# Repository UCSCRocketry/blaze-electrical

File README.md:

# blaze electrical
UC Santa Cruz Rocket Team's unified high power rocketry avionics project, electrical repository

[Notion Project Managment (Private)](https://ucscrocketry.notion.site/)

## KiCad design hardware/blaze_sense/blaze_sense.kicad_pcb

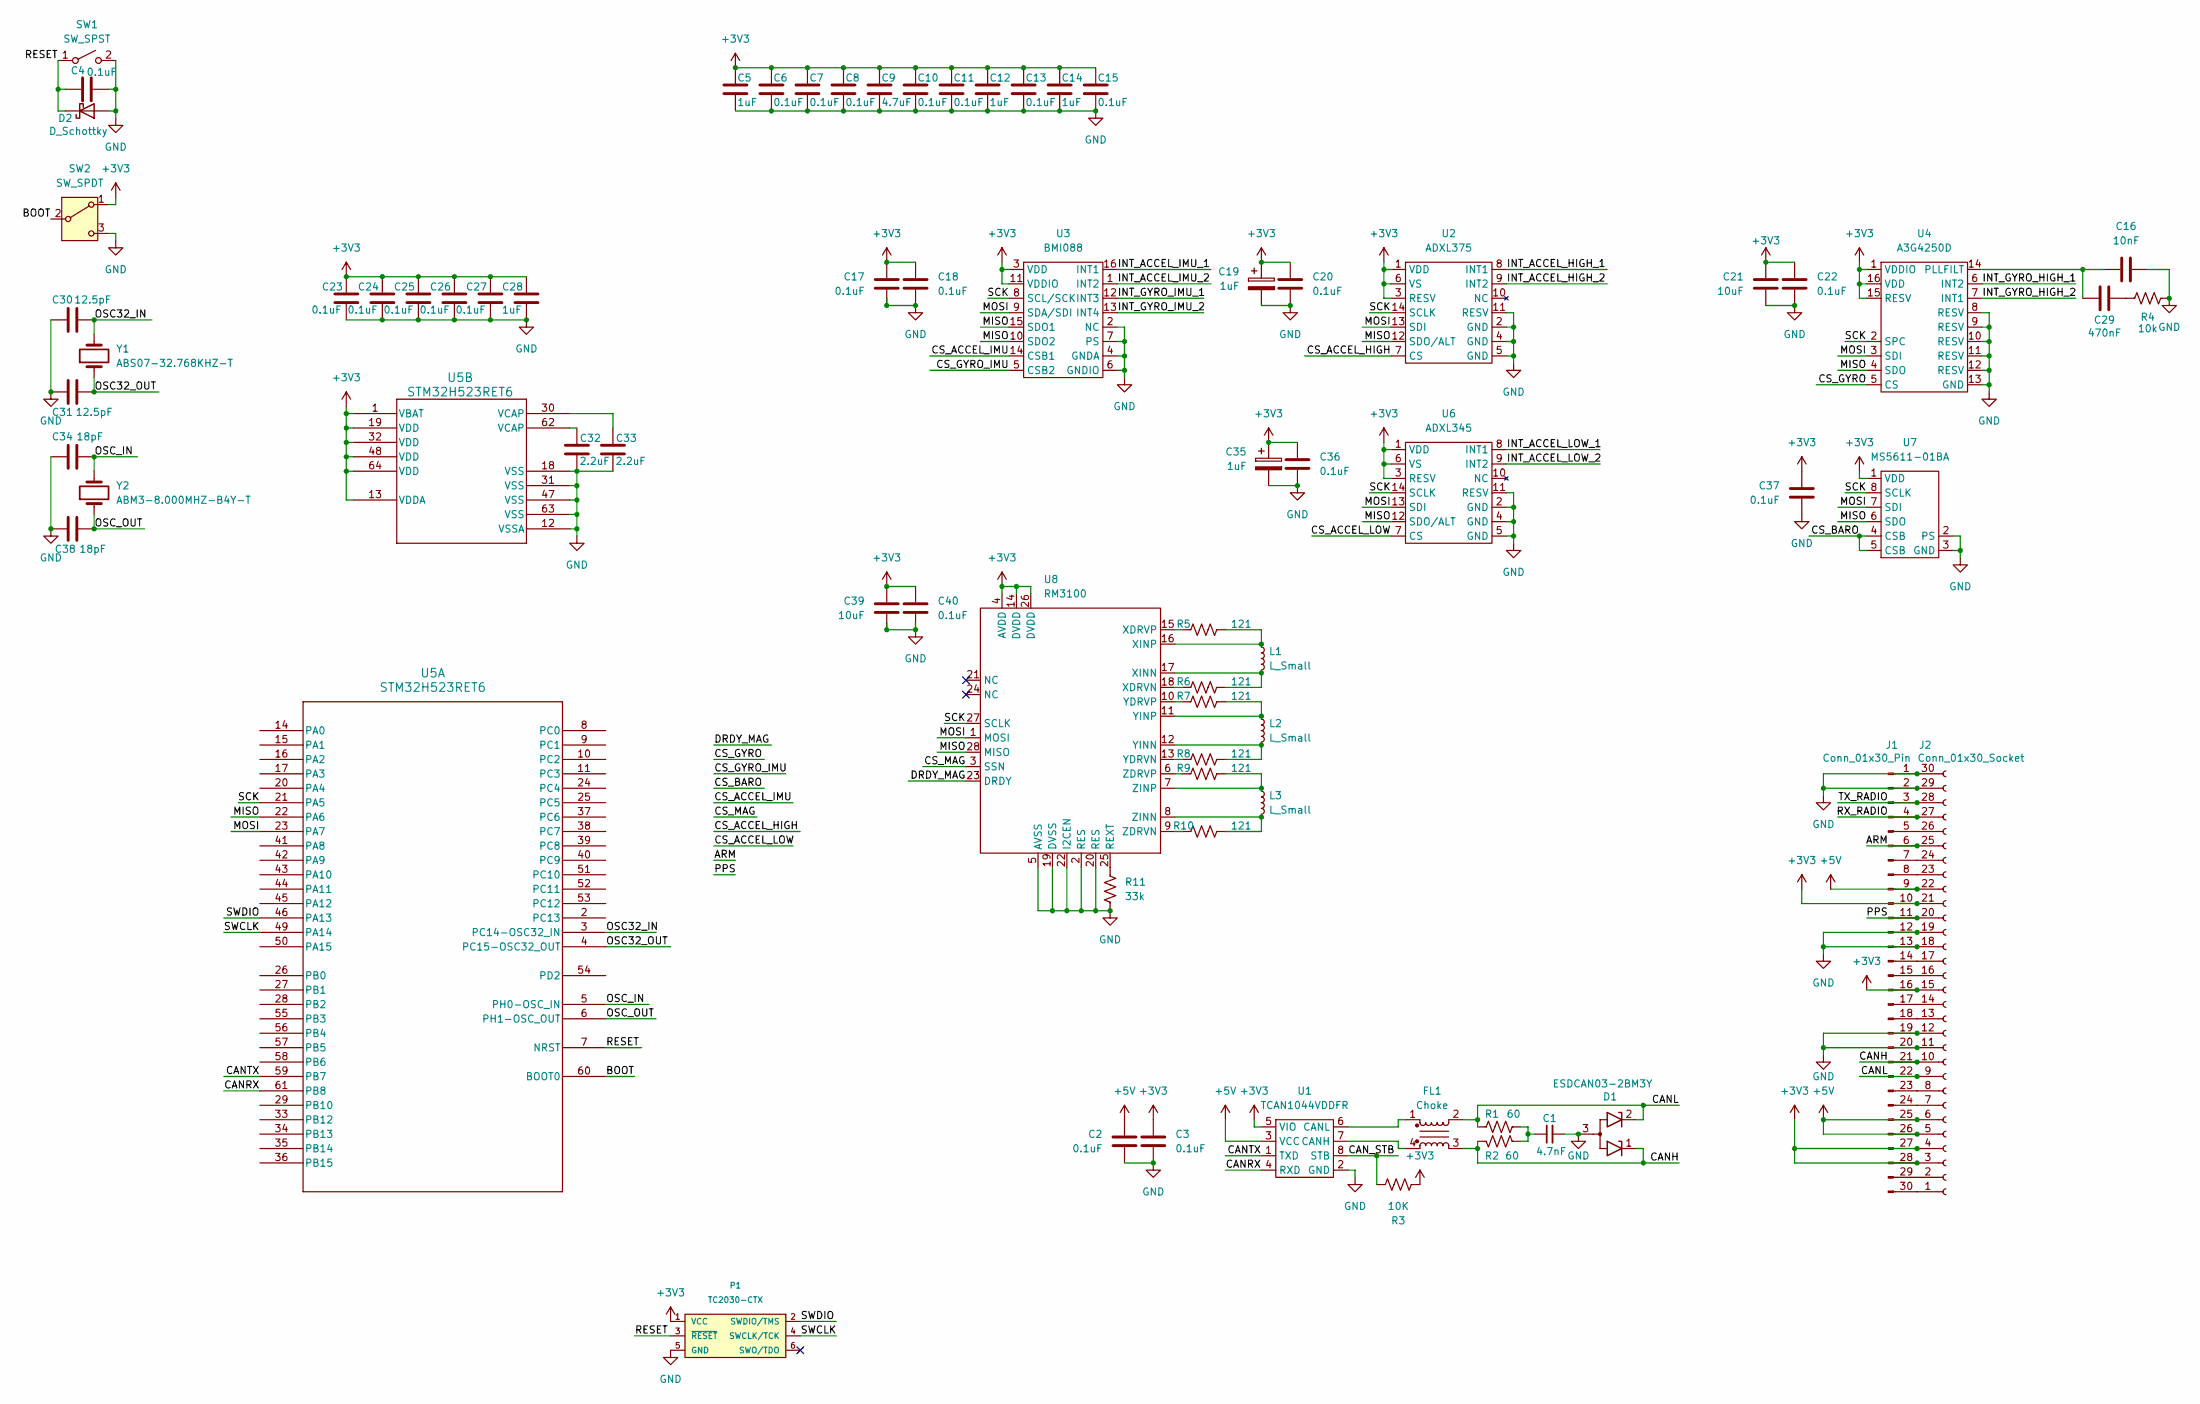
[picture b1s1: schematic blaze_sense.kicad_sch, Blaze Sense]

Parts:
C1: 4.7nF; C_0603_1608Metric
C2, C3, C4, C6, C7, C8, C10, C11, C13, C15, C17, C18, C20, C22, C23, C24, C25, C26, C27, C36, C37, C40: 0.1uF; C_0603_1608Metric
C5, C12, C14, C19, C28, C35: 1uF; C_0603_1608Metric
C9: 4.7uF; C_0603_1608Metric
C16: 10nF; C_0603_1608Metric
C21, C39: 10uF; C_0603_1608Metric
C29: 470nF; C_0603_1608Metric
C30, C31: 12.5pF; C_0603_1608Metric
C32, C33: 2.2uF; C_0603_1608Metric
C34, C38: 18pF; C_0603_1608Metric
D1: ESDCAN03-2BM3Y; SOT-416
D2: D_Schottky; D_0603_1608Metric
FL1: Choke; L_CommonModeChoke_Coilcraft_0603USB
J1: Conn_01x30_Pin; HRS_DF17_1.0H_-30DP-0.5V_57_
J2: Conn_01x30_Socket; HRS_DF17_1.0H_-30DP-0.5V_57_
L1, L2: L_Small; SENSOR-XY-F-RM3100
L3: L_Small; SENSOR-Z-F-RM3100
P1: TC2030-CTX; TC2030-IDC-FP
R1, R2: 60; R_0603_1608Metric
R3: 10K; R_0603_1608Metric
R4: 10k; R_0603_1608Metric
R5, R6, R7, R8, R9, R10: 121; R_0603_1608Metric
R11: 33k; R_0603_1608Metric
SW1: SW_SPST; SW_SPST_B3U-1000P
SW2: SW_SPDT; Nidec_Copal_CAS-120A
U1: TCAN1044VDDFR; Texas_VSON-HR-8_1.5x2mm_P0.5mm
U2: ADXL375; ADXL375BCCZ-RL
U3: BMI088
U4: A3G4250D
U5: STM32H523RET6; LQFP64_STM
U6: ADXL345
U7: MS5611-01BA; LGA-8_3x5mm_P1.25mm
U8: RM3100; RM3100-13156
Y1: ABS07-32.768KHZ-T; Crystal_SMD_3215-2Pin_3.2x1.5mm
Y2: ABM3-8.000MHZ-B4Y-T; Crystal_SMD_3215-2Pin_3.2x1.5mm

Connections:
+3V3: C3.1, C5.1, C6.1, C7.1, C8.1, C9.1, C10.1, C11.1, C12.1, C13.1, C14.1, C15.1, C17.1, C18.1, C19.1, C20.1, C21.1, C22.1, C23.1, C24.1, C25.1, C26.1, C27.1, C28.1, C35.1, C36.1, C37.1, C39.1, C40.1, J1.10, J1.16, J1.27, J1.28, J2.3, J2.4, J2.15, J2.21, P1.1 (VCC), R3.2, SW2.1 (A), U1.5 (VIO), U2.1 (VDD), U2.3 (RESV), U2.6 (VS), U3.3 (VDD), U3.11 (VDDIO), U4.1 (VDDIO), U4.15 (RESV), U4.16 (VDD), U5.1 (VBAT), U5.13 (VDDA), U5.19 (VDD), U5.32 (VDD), U5.48 (VDD), U5.64 (VDD), U6.1 (VDD), U6.3 (RESV), U6.6 (VS), U7.1 (VDD), U8.4 (AVDD), U8.14 (DVDD), U8.26 (DVDD)
+5V: C2.1, J1.9, J1.25, J1.26, J2.5, J2.6, J2.22, U1.3 (VCC)
/ARM: J1.6, J2.25
/BOOT: SW2.2 (B), U5.60 (BOOT0)
/CANH: D1.1 (K1), FL1.3, J1.21, J2.10, R2.1
/CANL: D1.2 (K2), FL1.2, J1.22, J2.9, R1.1
/CANRX: U1.4 (RXD), U5.61 (PB8)
/CANTX: U1.1 (TXD), U5.59 (PB7)
/CAN_STB: R3.1, U1.8 (STB)
/CS_ACCEL_HIGH: U2.7 (CS)
/CS_ACCEL_IMU: U3.14 (CSB1)
/CS_ACCEL_LOW: U6.7 (CS)
/CS_BARO: U7.4 (CSB), U7.5 (CSB)
/CS_GYRO: U4.5 (CS)
/CS_GYRO_IMU: U3.5 (CSB2)
/CS_MAG: U8.3 (SSN)
/DRDY_MAG: U8.23 (DRDY)
/INT_ACCEL_HIGH_1: U2.8 (INT1)
/INT_ACCEL_HIGH_2: U2.9 (INT2)
/INT_ACCEL_IMU_1: U3.16 (INT1)
/INT_ACCEL_IMU_2: U3.1 (INT2)
/INT_ACCEL_LOW_1: U6.8 (INT1)
/INT_ACCEL_LOW_2: U6.9 (INT2)
/INT_GYRO_HIGH_1: U4.6 (INT2)
/INT_GYRO_HIGH_2: U4.7 (INT1)
/INT_GYRO_IMU_1: U3.12 (INT3)
/INT_GYRO_IMU_2: U3.13 (INT4)
/MISO: U2.12 (SDO/ALT), U3.10 (SDO2), U3.15 (SDO1), U4.4 (SDO), U5.22 (PA6), U6.12 (SDO/ALT), U7.6 (SDO), U8.28 (MISO)
/MOSI: U2.13 (SDI), U3.9 (SDA/SDI), U4.3 (SDI), U5.23 (PA7), U6.13 (SDI), U7.7 (SDI), U8.1 (MOSI)
/OSC32_IN: C30.2, U5.3 (PC14-OSC32_IN), Y1.2
/OSC32_OUT: C31.2, U5.4 (PC15-OSC32_OUT), Y1.1
/OSC_IN: C34.2, U5.5 (PH0-OSC_IN), Y2.2
/OSC_OUT: C38.2, U5.6 (PH1-OSC_OUT), Y2.1
/PPS: J1.11, J2.20
/RESET: C4.1, D2.1 (K), P1.3 (~RESET), SW1.1 (A), U5.7 (NRST)
/RX_RADIO: J1.4, J2.27
/SCK: U2.14 (SCLK), U3.8 (SCL/SCK), U4.2 (SPC), U5.21 (PA5), U6.14 (SCLK), U7.8 (SCLK), U8.27 (SCLK)
/SWCLK: P1.4 (SWCLK/TCK), U5.49 (PA14)
/SWDIO: P1.2 (SWDIO/TMS), U5.46 (PA13)
/TX_RADIO: J1.3, J2.28
GND: C1.2, C2.2, C3.2, C4.2, C5.2, C6.2, C7.2, C8.2, C9.2, C10.2, C11.2, C12.2, C13.2, C14.2, C15.2, C16.2, C17.2, C18.2, C19.2, C20.2, C21.2, C22.2, C23.2, C24.2, C25.2, C26.2, C27.2, C28.2, C30.1, C31.1, C32.2, C33.2, C34.1, C35.2, C36.2, C37.2, C38.1, C39.2, C40.2, D1.3 (A), D2.2 (A), J1.1, J1.2, J1.12, J1.13, J1.19, J1.20, J2.11, J2.12, J2.18, J2.19, J2.29, J2.30, P1.5 (GND), R4.2, R11.2, SW1.2 (B), SW2.3 (C), U1.2 (GND), U2.2 (GND), U2.4 (GND), U2.5 (GND), U2.11 (RESV), U3.2 (NC), U3.4 (GNDA), U3.6 (GNDIO), U3.7 (PS), U4.8 (RESV), U4.9 (RESV), U4.10 (RESV), U4.11 (RESV), U4.12 (RESV), U4.13 (GND), U5.12 (VSSA), U5.18 (VSS), U5.31 (VSS), U5.47 (VSS), U5.63 (VSS), U6.2 (GND), U6.4 (GND), U6.5 (GND), U6.11 (RESV), U7.2 (PS), U7.3 (GND), U8.2 (RES), U8.5 (AVSS), U8.19 (DVSS), U8.20 (RES), U8.22 (I2CEN)
unnamed: C1.1, R1.2, R2.2
unnamed: C29.2, R4.1
unnamed: C32.1, U5.62 (VCAP)
unnamed: C33.1, U5.30 (VCAP)
unnamed: J1.5, J2.26
unnamed: J1.7, J2.24
unnamed: J1.8, J2.23
unnamed: J1.14, J2.17
unnamed: J1.15, J2.16
unnamed: J1.17, J2.14
unnamed: J1.18, J2.13
unnamed: J1.23, J2.8
unnamed: J1.24, J2.7
unnamed: J1.29, J2.2
unnamed: J1.30, J2.1
unnamed: FL1.4, U1.7 (CANH)
unnamed: FL1.1, U1.6 (CANL)
unnamed: C16.1, C29.1, U4.14 (PLLFILT)
unnamed: R11.1, U8.25 (REXT)
unnamed: R6.1, U8.18 (XDRVN)
unnamed: R5.1, U8.15 (XDRVP)
unnamed: L1.2, R6.2, U8.17 (XINN)
unnamed: L1.1, R5.2, U8.16 (XINP)
unnamed: R8.1, U8.13 (YDRVN)
unnamed: R7.1, U8.10 (YDRVP)
unnamed: L2.2, R8.2, U8.12 (YINN)
unnamed: L2.1, R7.2, U8.11 (YINP)
unnamed: R10.1, U8.9 (ZDRVN)
unnamed: R9.1, U8.6 (ZDRVP)
unnamed: L3.2, R10.2, U8.8 (ZINN)
unnamed: L3.1, R9.2, U8.7 (ZINP)

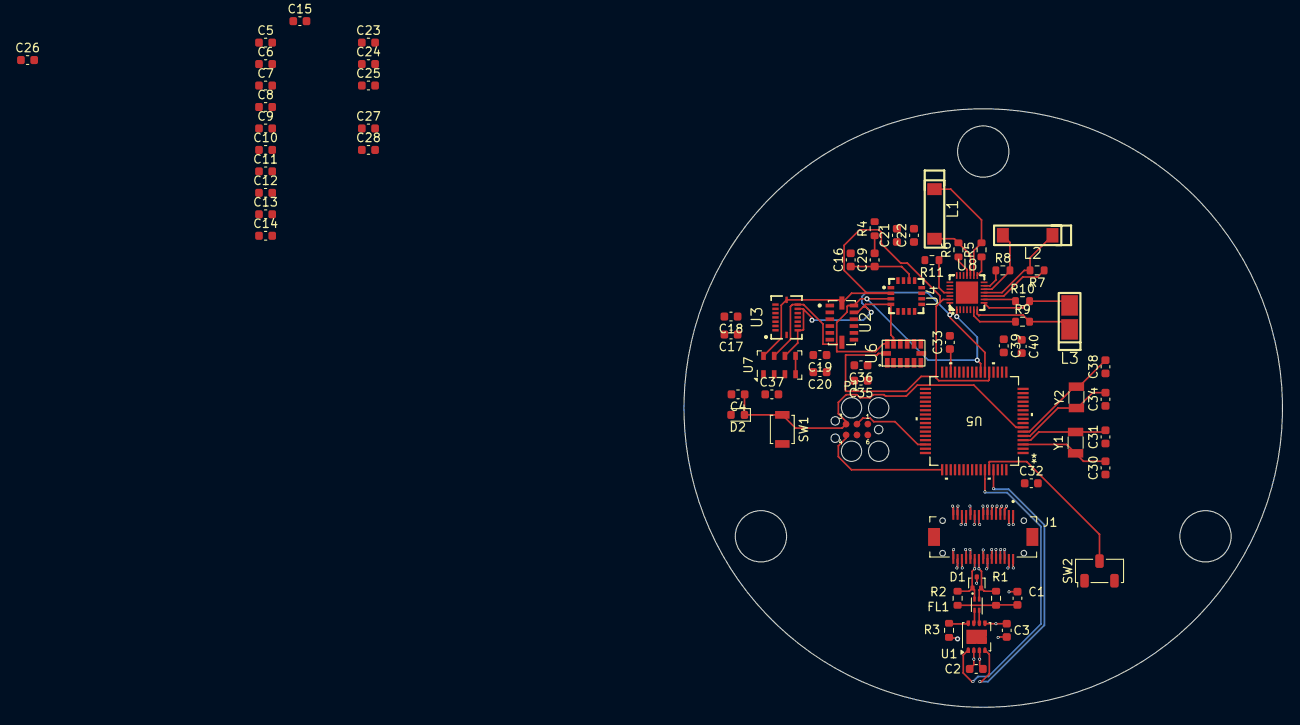
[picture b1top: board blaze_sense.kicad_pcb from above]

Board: 4 copper layers, 70.0 x 70.0 mm, 72 parts (1 on the bottom side), 55 nets.

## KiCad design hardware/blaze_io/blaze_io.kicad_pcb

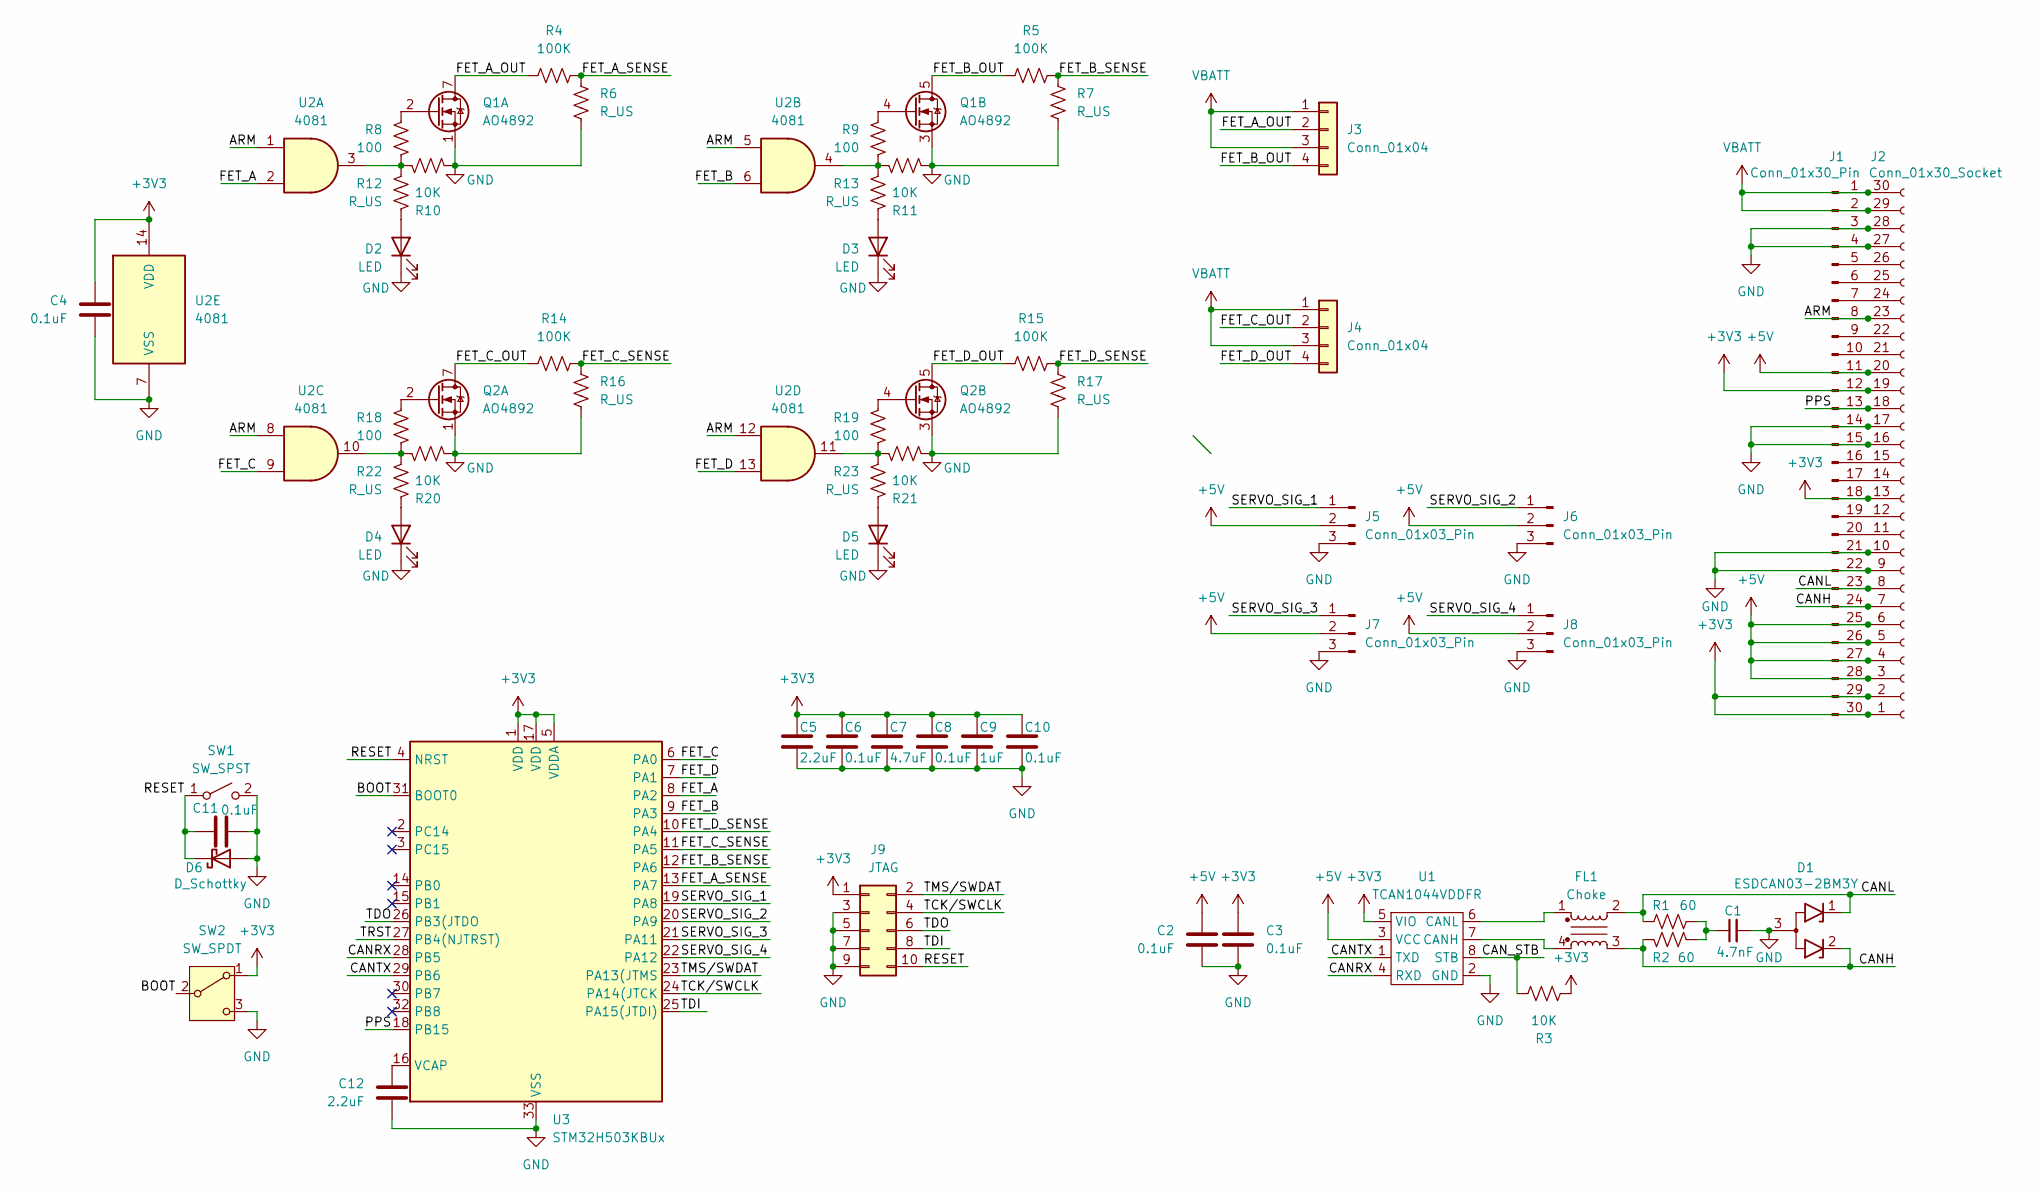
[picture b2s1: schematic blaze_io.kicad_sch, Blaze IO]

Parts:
C1: 4.7nF; C_0603_1608Metric
C2, C3, C4, C6, C8, C10, C11: 0.1uF; C_0603_1608Metric
C5, C12: 2.2uF; C_0603_1608Metric
C7: 4.7uF; C_0603_1608Metric
C9: 1uF; C_0603_1608Metric
D1: ESDCAN03-2BM3Y; SOT-416
D2, D3, D4, D5: LED; LED_0603_1608Metric
D6: D_Schottky; D_0603_1608Metric
FL1: Choke; L_CommonModeChoke_Coilcraft_0603USB
J1: Conn_01x30_Pin; HRS_DF17_1.0H_-30DP-0.5V_57_
J2: Conn_01x30_Socket; HRS_DF17_1.0H_-30DP-0.5V_57_
J3, J4: Conn_01x04; TerminalBlock_TE_282834-4_1x04_P2.54mm_Horizontal
J5, J6, J7, J8: Conn_01x03_Pin; PinHeader_1x03_P2.54mm_Vertical
J9: JTAG; PinHeader_2x05_P2.54mm_Vertical
Q1, Q2: AO4892; SOIC-8_3.9x4.9mm_P1.27mm
R1, R2: 60; R_0603_1608Metric
R3, R10, R11, R20, R21: 10K; R_0603_1608Metric
R4, R5, R14, R15: 100K; R_0603_1608Metric
R6, R7, R12, R13, R16, R17, R22, R23: R_US; R_0603_1608Metric
R8, R9, R18, R19: 100; R_0603_1608Metric
SW1: SW_SPST; SW_SPST_B3U-1000P
SW2: SW_SPDT; Nidec_Copal_CAS-120A
U1: TCAN1044VDDFR; Texas_VSON-HR-8_1.5x2mm_P0.5mm
U2: 4081; SOIC-14_3.9x8.7mm_P1.27mm
U3: STM32H503KBUx; QFN-32-1EP_5x5mm_P0.5mm_EP3.45x3.45mm

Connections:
+3V3: C3.1, C4.1, C5.1, C6.1, C7.1, C8.1, C9.1, C10.1, J1.12, J1.18, J1.29, J1.30, J2.1, J2.2, J2.13, J2.19, J9.1, R3.2, SW2.1 (A), U1.5 (VIO), U2.14 (VDD), U3.1 (VDD), U3.5 (VDDA), U3.17 (VDD)
+5V: C2.1, J1.11, J1.25, J1.26, J1.27, J1.28, J2.3, J2.4, J2.5, J2.6, J2.20, J5.2, J6.2, J7.2, J8.2, U1.3 (VCC)
/ARM: J1.8, J2.23, U2.1, U2.5, U2.8, U2.12
/BOOT: SW2.2 (B), U3.31 (BOOT0)
/CANH: D1.2 (K2), FL1.3, J1.24, J2.7, R2.1
/CANL: D1.1 (K1), FL1.2, J1.23, J2.8, R1.1
/CANRX: U1.4 (RXD), U3.28 (PB5)
/CANTX: U1.1 (TXD), U3.29 (PB6)
/CAN_STB: R3.1, U1.8 (STB)
/FET_A: U2.2, U3.8 (PA2)
/FET_A_OUT: J3.2, Q1.7 (D1), Q1.8 (D1), R4.1
/FET_A_SENSE: R4.2, R6.2, U3.13 (PA7)
/FET_B: U2.6, U3.9 (PA3)
/FET_B_OUT: J3.4, Q1.5 (D2), Q1.6 (D2), R5.1
/FET_B_SENSE: R5.2, R7.2, U3.12 (PA6)
/FET_C: U2.9, U3.6 (PA0)
/FET_C_OUT: J4.2, Q2.7 (D1), Q2.8 (D1), R14.1
/FET_C_SENSE: R14.2, R16.2, U3.11 (PA5)
/FET_D: U2.13, U3.7 (PA1)
/FET_D_OUT: J4.4, Q2.5 (D2), Q2.6 (D2), R15.1
/FET_D_SENSE: R15.2, R17.2, U3.10 (PA4)
/PPS: J1.13, J2.18, U3.18 (PB15)
/RESET: C11.1, D6.1 (K), J9.10, SW1.1 (A), U3.4 (NRST)
/SERVO_SIG_1: J5.1, U3.19 (PA8)
/SERVO_SIG_2: J6.1, U3.20 (PA9)
/SERVO_SIG_3: J7.1, U3.21 (PA11)
/SERVO_SIG_4: J8.1, U3.22 (PA12)
/TCK/SWCLK: J9.4, U3.24 (PA14(JTCK)
/TDI: J9.8, U3.25 (PA15(JTDI))
/TDO: J9.6, U3.26 (PB3(JTDO)
/TMS/SWDAT: J9.2, U3.23 (PA13(JTMS)
/TRST: U3.27 (PB4(NJTRST))
GND: C1.2, C2.2, C3.2, C4.2, C5.2, C6.2, C7.2, C8.2, C9.2, C10.2, C11.2, C12.2, D1.3 (A), D2.1 (K), D3.1 (K), D4.1 (K), D5.1 (K), D6.2 (A), J1.3, J1.4, J1.14, J1.15, J1.21, J1.22, J2.9, J2.10, J2.16, J2.17, J2.27, J2.28, J5.3, J6.3, J7.3, J8.3, J9.3, J9.5, J9.7, J9.9, Q1.1 (S1), Q1.3 (S2), Q2.1 (S1), Q2.3 (S2), R6.1, R7.1, R10.2, R11.2, R16.1, R17.1, R20.2, R21.2, SW1.2 (B), SW2.3 (C), U1.2 (GND), U2.7 (VSS), U3.33 (VSS)
unnamed: C1.1, R1.2, R2.2
unnamed: D2.2 (A), R12.2
unnamed: D3.2 (A), R13.2
unnamed: D4.2 (A), R22.2
unnamed: D5.2 (A), R23.2
unnamed: J1.5, J2.26
unnamed: J1.6, J2.25
unnamed: J1.7, J2.24
unnamed: J1.9, J2.22
unnamed: J1.10, J2.21
unnamed: J1.16, J2.15
unnamed: J1.17, J2.14
unnamed: J1.19, J2.12
unnamed: J1.20, J2.11
unnamed: Q1.2 (G1), R8.1
unnamed: Q1.4 (G2), R9.1
unnamed: Q2.2 (G1), R18.1
unnamed: Q2.4 (G2), R19.1
unnamed: R8.2, R10.1, R12.1, U2.3
unnamed: R9.2, R11.1, R13.1, U2.4
unnamed: R18.2, R20.1, R22.1, U2.10
unnamed: R19.2, R21.1, R23.1, U2.11
unnamed: FL1.4, U1.7 (CANH)
unnamed: FL1.1, U1.6 (CANL)
unnamed: C12.1, U3.16 (VCAP)
VBATT: J1.1, J1.2, J2.29, J2.30, J3.1, J3.3, J4.1, J4.3

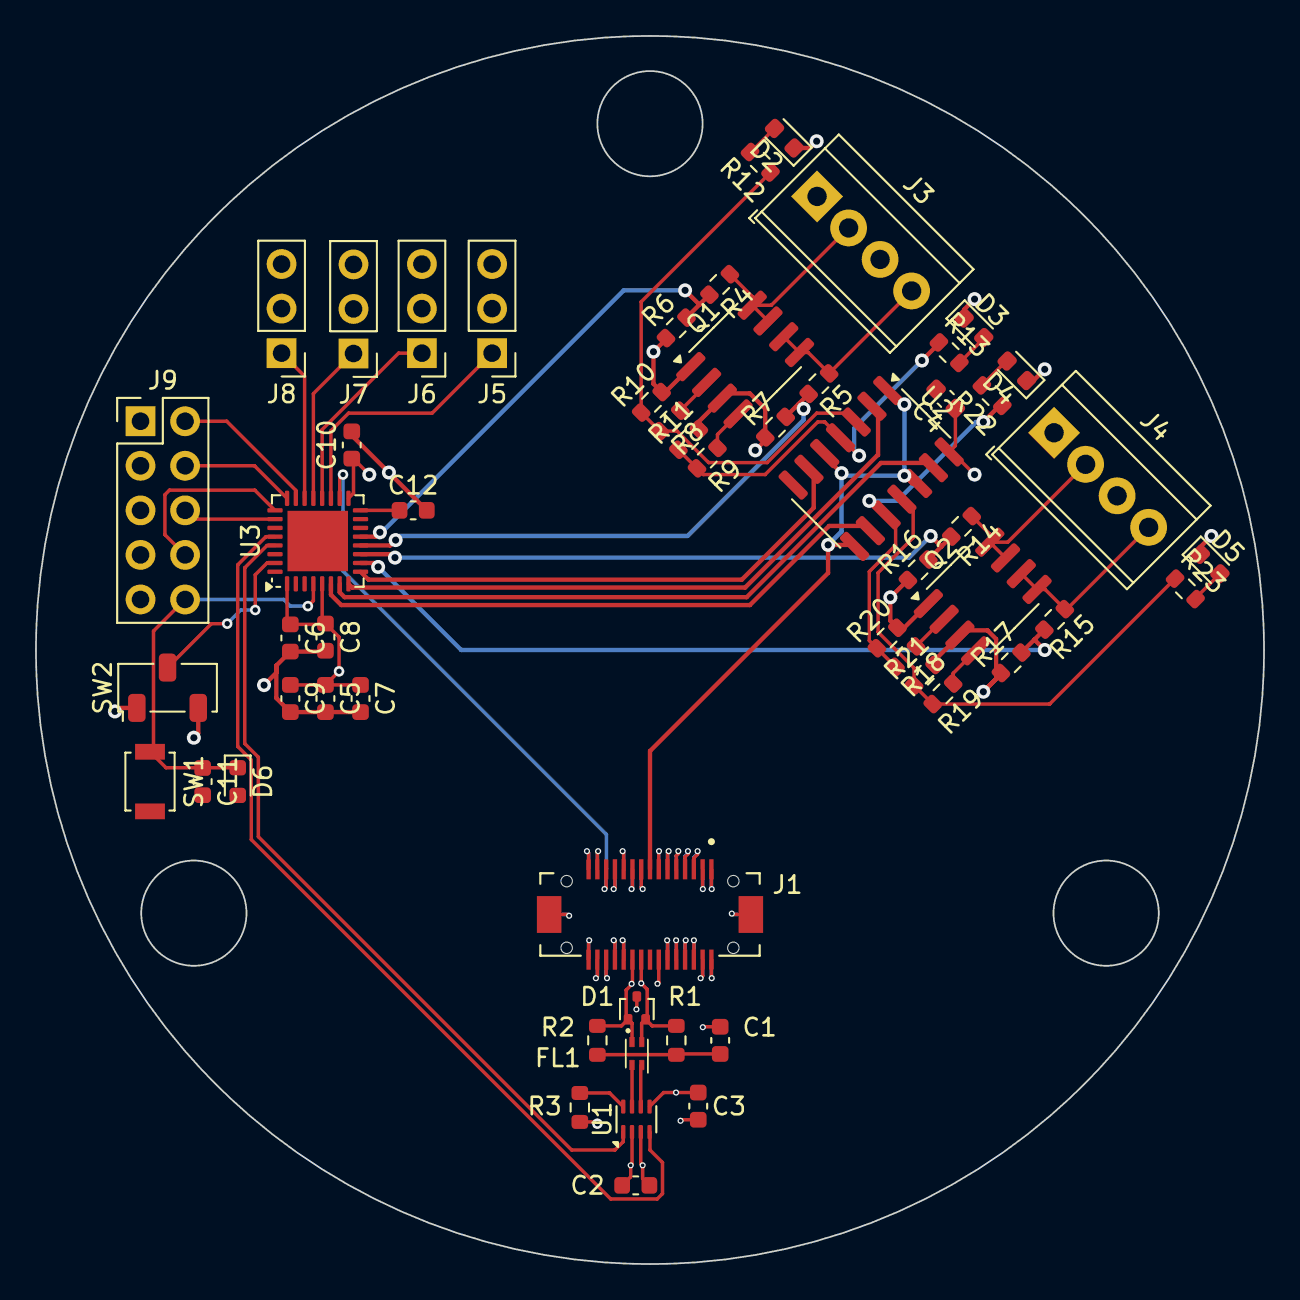
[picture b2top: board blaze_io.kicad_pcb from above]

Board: 4 copper layers, 70.0 x 70.0 mm, 58 parts (1 on the bottom side), 58 nets.

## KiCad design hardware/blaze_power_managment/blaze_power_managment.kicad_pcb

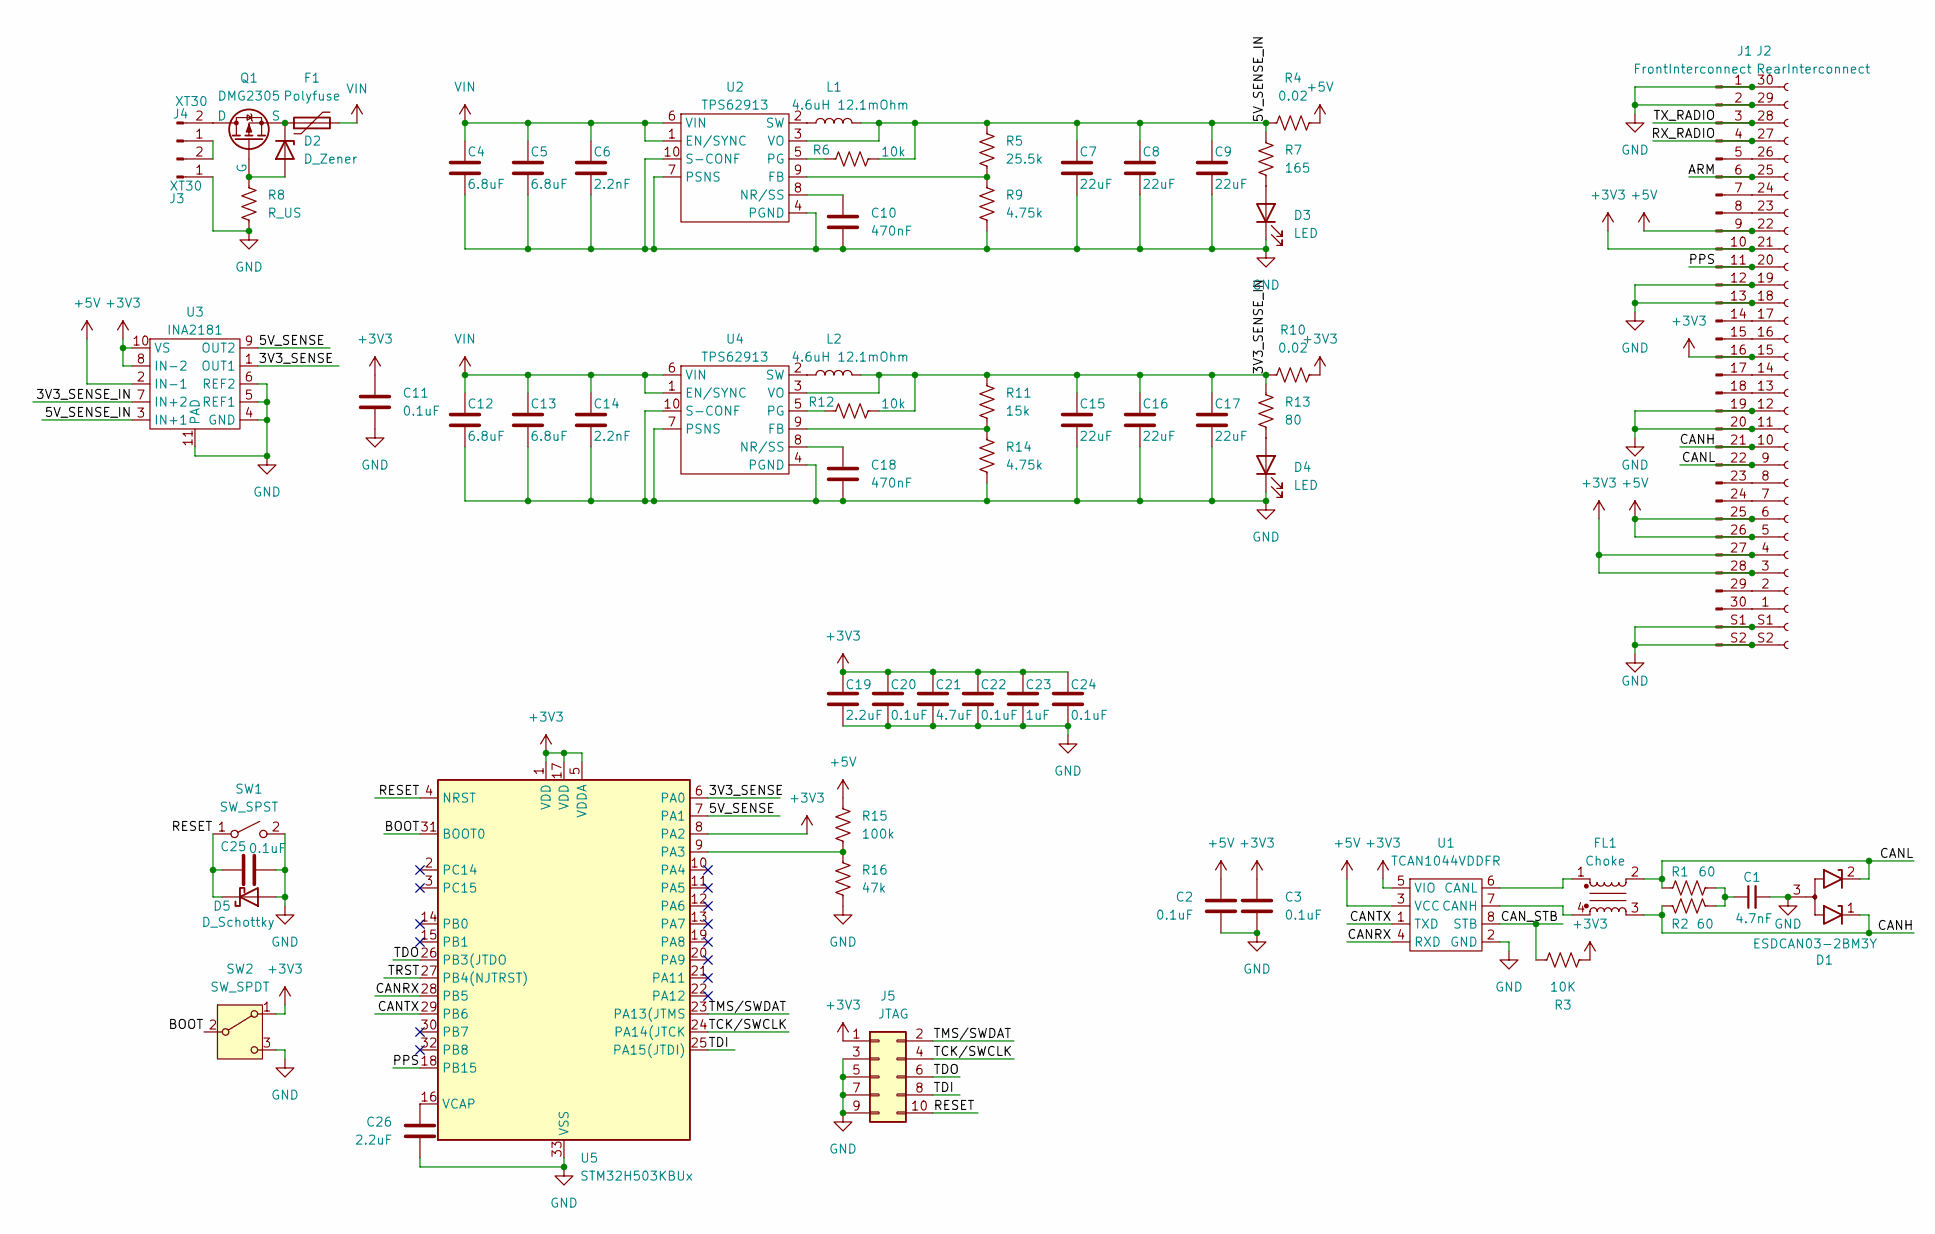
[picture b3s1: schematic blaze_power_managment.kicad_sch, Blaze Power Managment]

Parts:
C1: 4.7nF; C_0603_1608Metric
C2, C3, C11, C20, C22, C24, C25: 0.1uF; C_0603_1608Metric
C4, C5, C12, C13: 6.8uF; C_0603_1608Metric
C6, C14: 2.2nF; C_0603_1608Metric
C7, C8, C9, C15, C16, C17: 22uF; C_0603_1608Metric
C10, C18: 470nF; C_0603_1608Metric
C19, C26: 2.2uF; C_0603_1608Metric
C21: 4.7uF; C_0603_1608Metric
C23: 1uF; C_0603_1608Metric
D1: ESDCAN03-2BM3Y; SOT-416
D2: D_Zener; D_0603_1608Metric
D3, D4: LED; LED_0603_1608Metric
D5: D_Schottky; D_0603_1608Metric
F1: Polyfuse; Fuse_1206_3216Metric
FL1: Choke; L_CommonModeChoke_Coilcraft_0603USB
J1: FrontInterconnect; HRS_DF17_1.0H_-30DP-0.5V_57_
J2: RearInterconnect; HRS_DF17_1.0H_-30DP-0.5V_57_
J3, J4: XT30; AMASS_XT30PW-M_1x02_P2.50mm_Horizontal
J5: JTAG; PinHeader_2x05_P1.00mm_Vertical_SMD
L1, L2: 4.6uH 12.1mOhm; L_SXN_SMDRI124
Q1: DMG2305; SOT-23-3
R1, R2: 60; R_0603_1608Metric
R3: 10K; R_0603_1608Metric
R4, R10: 0.02; R_0603_1608Metric
R5: 25.5k; R_0603_1608Metric
R6, R12: 10k; R_0603_1608Metric
R7: 165; R_0603_1608Metric
R8: R_US; R_0603_1608Metric
R9, R14: 4.75k; R_0603_1608Metric
R11: 15k; R_0603_1608Metric
R13: 80; R_0603_1608Metric
R15: 100k; R_0603_1608Metric
R16: 47k; R_0603_1608Metric
SW1: SW_SPST; SW_SPST_B3U-1000P
SW2: SW_SPDT; Nidec_Copal_CAS-120A
U1: TCAN1044VDDFR; Texas_VSON-HR-8_1.5x2mm_P0.5mm
U2, U4: TPS62913; TPS62913R
U3: INA2181; WSON10-DSQ0010A_TEX
U5: STM32H503KBUx; QFN-32-1EP_5x5mm_P0.5mm_EP3.45x3.45mm

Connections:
+3V3: C3.1, C11.1, C19.1, C20.1, C21.1, C22.1, C23.1, C24.1, J1.10, J1.16, J1.27, J1.28, J2.3, J2.4, J2.15, J2.21, J5.1, R3.2, R10.2, SW2.1 (A), U1.5 (VIO), U3.8 (IN-2), U3.10 (VS), U5.1 (VDD), U5.5 (VDDA), U5.8 (PA2), U5.17 (VDD)
+5V: C2.1, J1.9, J1.25, J1.26, J2.5, J2.6, J2.22, R4.2, R15.1, U1.3 (VCC), U3.2 (IN-1)
/3V3_SENSE: U3.1 (OUT1), U5.6 (PA0)
/3V3_SENSE_IN: C15.1, C16.1, C17.1, L2.2, R10.1, R11.1, R12.2, R13.1, U3.7 (IN+2), U4.3 (VO)
/5V_SENSE: U3.9 (OUT2), U5.7 (PA1)
/5V_SENSE_IN: C7.1, C8.1, C9.1, L1.2, R4.1, R5.1, R6.2, R7.1, U2.3 (VO), U3.3 (IN+1)
/ARM: J1.6, J2.25
/BOOT: SW2.2 (B), U5.31 (BOOT0)
/CANH: D1.1 (K1), FL1.3, J1.21, J2.10, R2.1
/CANL: D1.2 (K2), FL1.2, J1.22, J2.9, R1.1
/CANRX: U1.4 (RXD), U5.28 (PB5)
/CANTX: U1.1 (TXD), U5.29 (PB6)
/CAN_STB: R3.1, U1.8 (STB)
/PPS: J1.11, J2.20, U5.18 (PB15)
/RESET: C25.1, D5.1 (K), J5.10, SW1.1 (A), U5.4 (NRST)
/RX_RADIO: J1.4, J2.27
/TCK/SWCLK: J5.4, U5.24 (PA14(JTCK)
/TDI: J5.8, U5.25 (PA15(JTDI))
/TDO: J5.6, U5.26 (PB3(JTDO)
/TMS/SWDAT: J5.2, U5.23 (PA13(JTMS)
/TRST: U5.27 (PB4(NJTRST))
/TX_RADIO: J1.3, J2.28
GND: C1.2, C2.2, C3.2, C4.2, C5.2, C6.2, C7.2, C8.2, C9.2, C10.2, C11.2, C12.2, C13.2, C14.2, C15.2, C16.2, C17.2, C18.2, C19.2, C20.2, C21.2, C22.2, C23.2, C24.2, C25.2, C26.2, D1.3 (A), D3.1 (K), D4.1 (K), D5.2 (A), J1.1, J1.2, J1.12, J1.13, J1.19, J1.20, J1.S1 (Tab_1), J1.S2 (Tab_2), J2.11, J2.12, J2.18, J2.19, J2.29, J2.30, J2.S1 (Tab_1), J2.S2 (Tab_2), J3.1, J5.3, J5.5, J5.7, J5.9, R8.2, R9.2, R14.2, R16.2, SW1.2 (B), SW2.3 (C), U1.2 (GND), U2.4 (PGND), U2.7 (PSNS), U2.10 (S-CONF), U3.4 (GND), U3.5 (REF1), U3.6 (REF2), U3.11 (PAD), U4.4 (PGND), U4.7 (PSNS), U4.10 (S-CONF), U5.33 (VSS)
unnamed: C1.1, R1.2, R2.2
unnamed: D2.2 (A), Q1.2 (G), R8.1
unnamed: D2.1 (K), F1.1, Q1.3 (S)
unnamed: D3.2 (A), R7.2
unnamed: D4.2 (A), R13.2
unnamed: J1.5, J2.26
unnamed: J1.7, J2.24
unnamed: J1.8, J2.23
unnamed: J1.14, J2.17
unnamed: J1.15, J2.16
unnamed: J1.17, J2.14
unnamed: J1.18, J2.13
unnamed: J1.23, J2.8
unnamed: J1.24, J2.7
unnamed: J1.29, J2.2
unnamed: J1.30, J2.1
unnamed: J3.2, J4.1
unnamed: J4.2, Q1.1 (D)
unnamed: FL1.4, U1.7 (CANH)
unnamed: FL1.1, U1.6 (CANL)
unnamed: R5.2, R9.1, U2.9 (FB)
unnamed: C10.1, U2.8 (NR/SS)
unnamed: R6.1, U2.5 (PG)
unnamed: L1.1, U2.2 (SW)
unnamed: R11.2, R14.1, U4.9 (FB)
unnamed: C18.1, U4.8 (NR/SS)
unnamed: R12.1, U4.5 (PG)
unnamed: L2.1, U4.2 (SW)
unnamed: R15.2, R16.1, U5.9 (PA3)
unnamed: C26.1, U5.16 (VCAP)
VIN: C4.1, C5.1, C6.1, C12.1, C13.1, C14.1, F1.2, U2.1 (EN/SYNC), U2.6 (VIN), U4.1 (EN/SYNC), U4.6 (VIN)

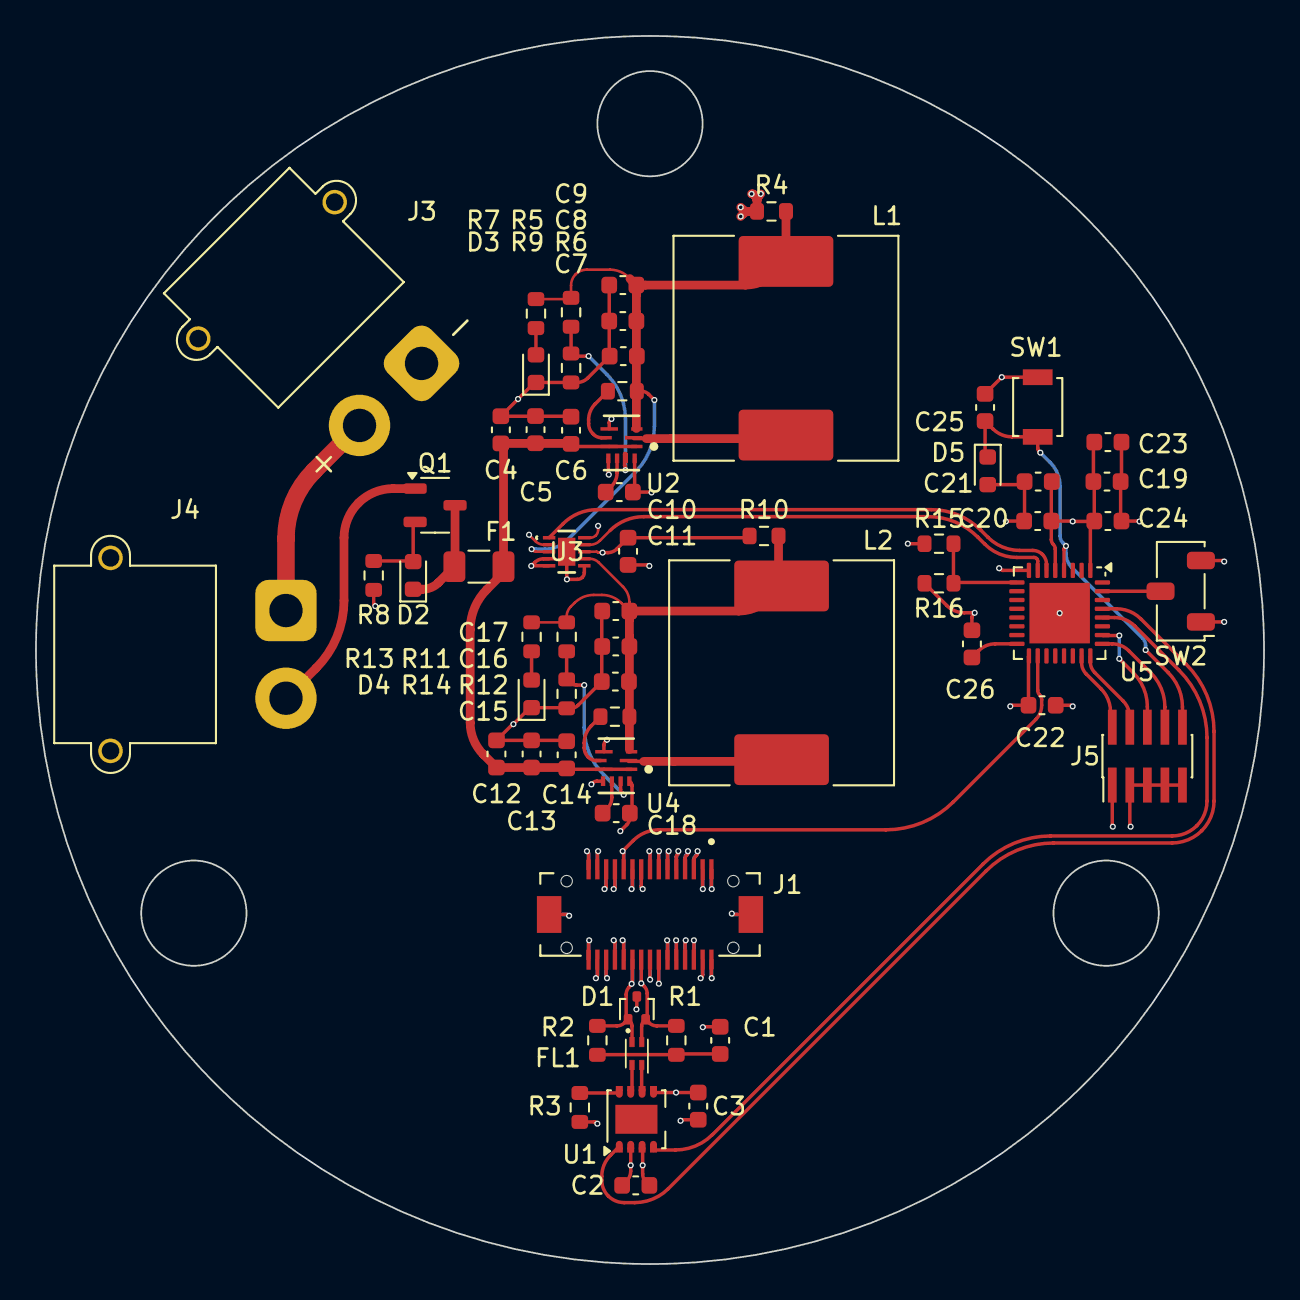
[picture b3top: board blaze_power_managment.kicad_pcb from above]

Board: 4 copper layers, 70.0 x 70.0 mm, 64 parts (1 on the bottom side), 53 nets.

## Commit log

2024-02-28 Edited Licenses
    Added hardware license, CERN Open Hardware Licence Version 2 – Weakly Reciprocal
2024-03-05 Initialized electrical documentation
2024-03-05 Formatting
2024-03-05 Initial Pinout mapping
2024-03-05 Added pin assingment table for interconnect
2024-03-06 Filled out pin mapping
2024-03-06 try to fix table
2024-04-22 Added Avionics Software Stack
2024-04-22 fixed table
2024-04-24 Added sensors for sensor board
2024-05-13 Created brain board schematic
2024-05-23 Removed software
2024-08-19 Part selection and license update
2024-08-19 Power
    Added power symbols and regulation
2024-08-19 Data Connections
2024-08-19 Decoupling and power
    Added decoupling capacitors as well as other power protection features
2024-08-27 Added current sensing
2024-08-27 Updated UNA2181 symbol
2024-08-27 Moved stuff around
2024-09-13 Created blaze power managmant
2024-09-13 Moved main power function to power management
2024-09-19 Created blaze sense, updated brain
2024-09-20 Created blaze io
2024-09-20 Connected IO, wrote docs
2024-09-20 Updated IO title block
2024-09-23 Created Blaze GPS
2024-09-24 Added capacitors, connected gps uart
2024-09-24 Filled in title block for GPS
2024-09-24 Created Blaze Radio
2024-09-26 Added CAN to Blaze Brain
2024-09-26 Connected Blaze Brain CAN
2024-10-02 Switched arm to active high and added to interconnect
2024-10-02 Added ARM AND gates to IO board
2024-10-03 Wrote power managmetn documentation
2024-10-04 Spelling corrections
2024-10-05 Formatting correction
2024-10-06 Wrote IO documentation
2024-10-06 Wrote GNSS documentation
2024-10-06 Wrote brain documentation
2024-10-06 Wrote common documentation
2024-10-06 Added co-processor to common documentation
2024-10-15 Added servo outputs
2024-10-15 Added PWM outputs to microcontroller
2024-11-19 Removed audio, neopixel, can2 from interconnect
2025-01-18 Brain Footprint Assignment
2025-01-18 GPS Footprint Assingments
2025-01-18 IO Footprint Assignments
2025-01-18 PowerMan Footprint Assignments
2025-01-19 Radio Footprint Assignments
2025-01-19 Sense Footprint Assignments
2025-01-20 Added mirror interconnect and PCB to brain
2025-01-20 Added mirror interconnect and PCB to sense
2025-01-20 Added mirror interconnect and PCB to radio
2025-01-20 Added mirror interconnect and PCB to io
2025-01-20 Added mirror interconnect and PCB to gps
2025-01-20 Added footprints
2025-01-24 Created reference templates for schematic and PCB work
2025-02-02 Updated schem and PCB references
2025-02-02 Brought in PCB template
2025-02-02 Initial component positioning
2025-02-02 Connected radio UART
2025-02-04 Added 3D models
2025-02-04 Moved template
2025-02-07 Routed board
2025-02-08 Component assingment
2025-02-08 Component grouping
2025-02-08 Power layout
2025-02-08 Component layout draft
2025-02-08 Designator placement
2025-02-08 Tracking more files
2025-02-09 Completed initial routing
2025-02-09 power routing
2025-02-09 Added voltage sensing
2025-02-09 Fixed via size
2025-02-09 Repaired misisng via connections
    CANH, CANL, unassigned, were not connected on back side
2025-02-11 Added Fillets
2025-02-11 Silkscreen Update
2025-02-13 Updated routing, rounded tracks
2025-02-22 Pyro grouping
2025-02-22 Component layout
2025-02-25 PCB Work
2025-03-02 Brought in template PCB
2025-03-02 Changed MCU
2025-03-03 draft for julian to look over
2025-03-03 Removed extra interconnect footprints
2025-03-03 Updated annotation
2025-03-03 Removed redundant CAN footprints
2025-03-03 Repaired CAN routing
